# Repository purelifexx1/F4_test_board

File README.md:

# F4_test_board
 This project includes code and schemetic of STM32F407VG discovery test board

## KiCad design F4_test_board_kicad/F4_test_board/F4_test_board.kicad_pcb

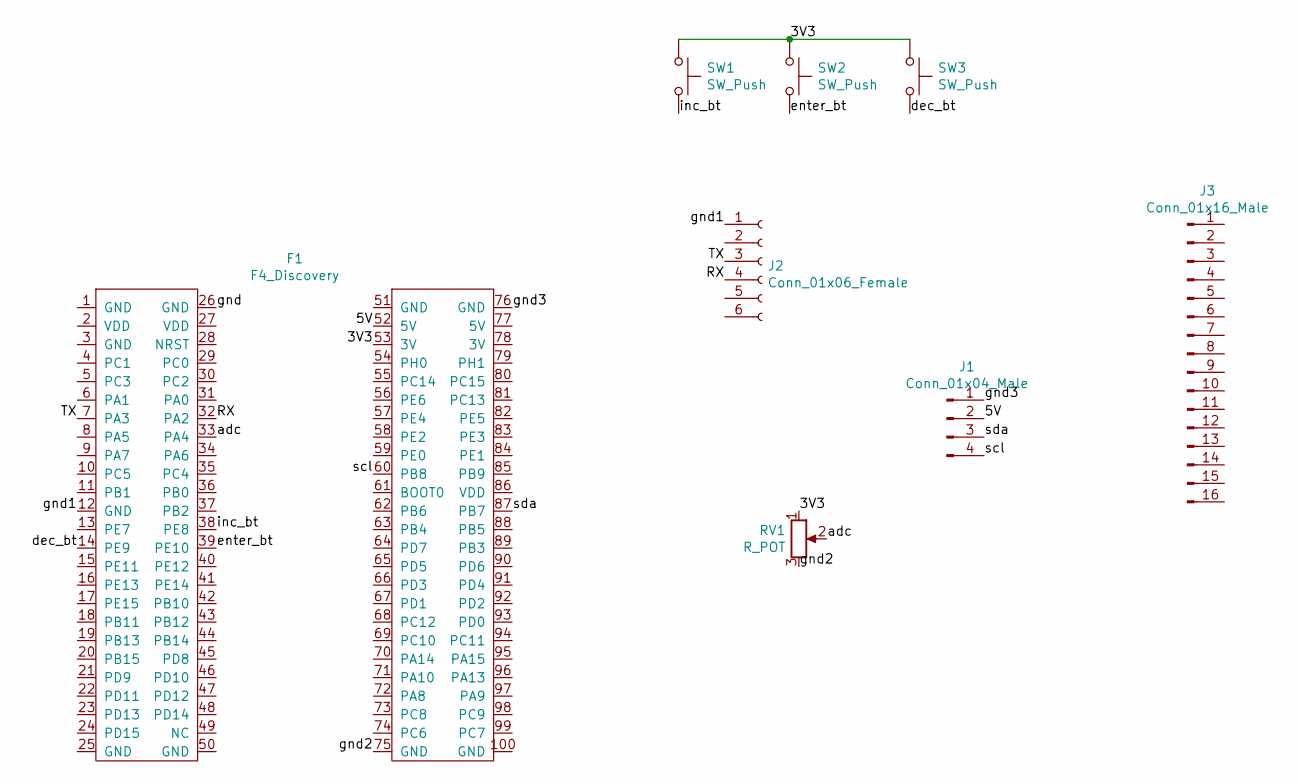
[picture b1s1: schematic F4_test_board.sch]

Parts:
F1: F4_Discovery; F4_discovery
J1: Conn_01x04_Male; PinSocket_1x04_P2.54mm_Vertical
J2: Conn_01x06_Female; PinSocket_1x06_P2.54mm_Vertical
J3: Conn_01x16_Male; PinSocket_1x16_P2.54mm_Vertical
RV1: R_POT; TerminalBlock_bornier-3_P5.08mm
SW1, SW2, SW3: SW_Push; SW_DIP_SPSTx01_Slide_9.78x4.72mm_W7.62mm_P2.54mm

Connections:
/3V3: F1.53 (3V), RV1.1, SW1.1, SW2.1, SW3.1
/5V: F1.52 (5V), J1.2
/RX: F1.32 (PA2), J2.4
/TX: F1.7 (PA3), J2.3
/adc: F1.33 (PA4), RV1.2
/dec_bt: F1.14 (PE9), SW3.2
/enter_bt: F1.39 (PE10), SW2.2
/gnd: F1.26 (GND)
/gnd1: F1.12 (GND), J2.1
/gnd2: F1.75 (GND), RV1.3
/gnd3: F1.76 (GND), J1.1
/inc_bt: F1.38 (PE8), SW1.2
/scl: F1.60 (PB8), J1.4
/sda: F1.87 (PB7), J1.3

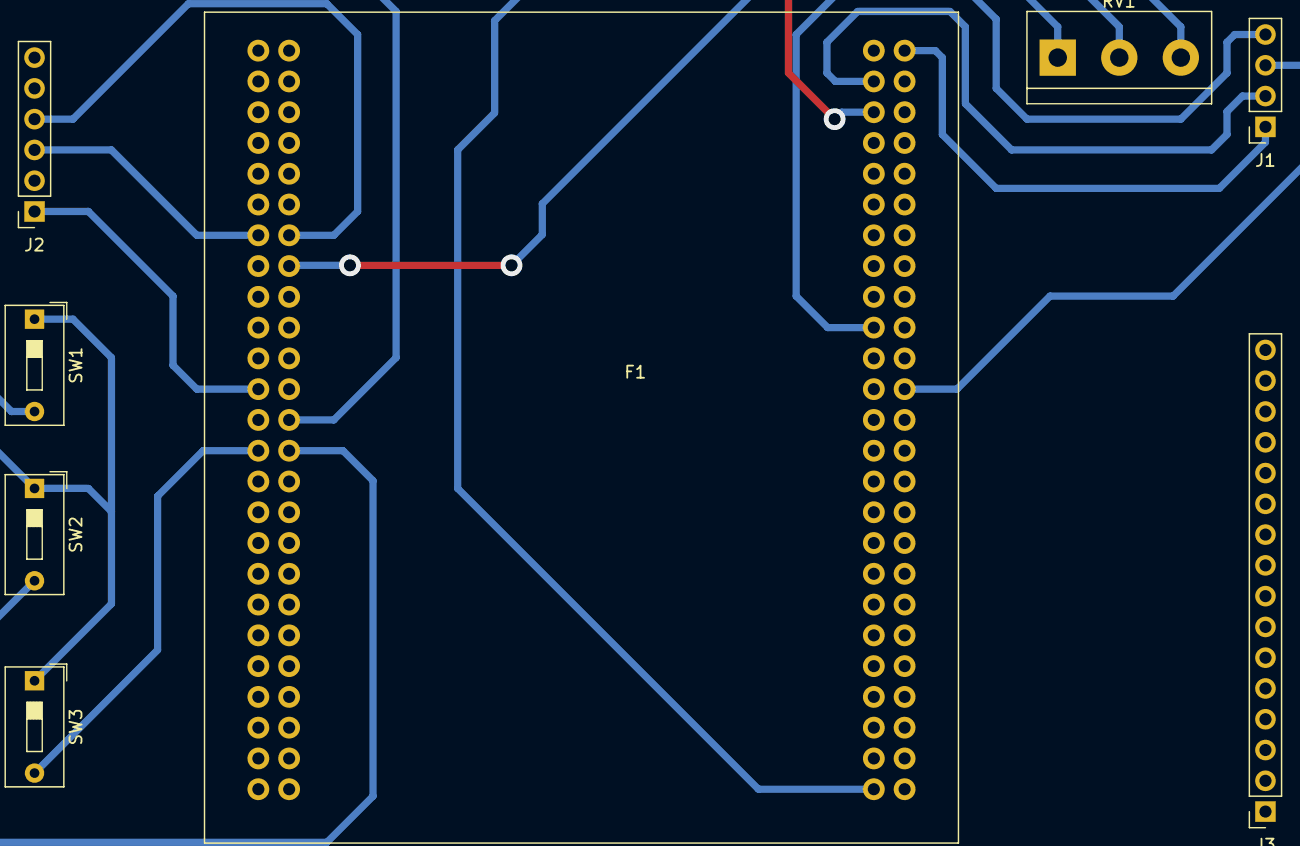
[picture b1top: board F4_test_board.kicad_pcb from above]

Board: 2 copper layers, 8 parts (0 on the bottom side), 13 nets.

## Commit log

2021-04-01 first attempt
